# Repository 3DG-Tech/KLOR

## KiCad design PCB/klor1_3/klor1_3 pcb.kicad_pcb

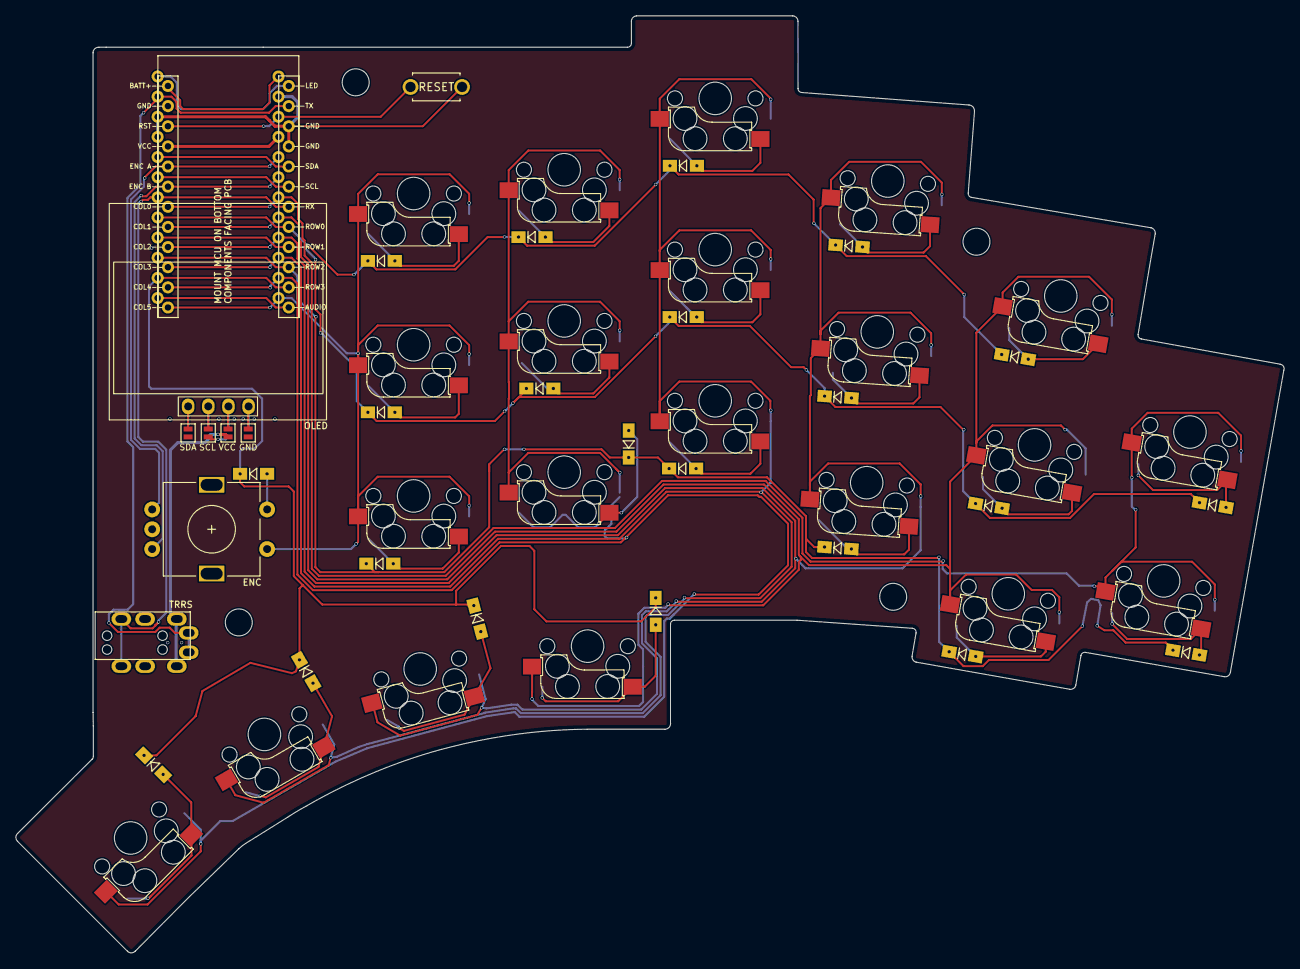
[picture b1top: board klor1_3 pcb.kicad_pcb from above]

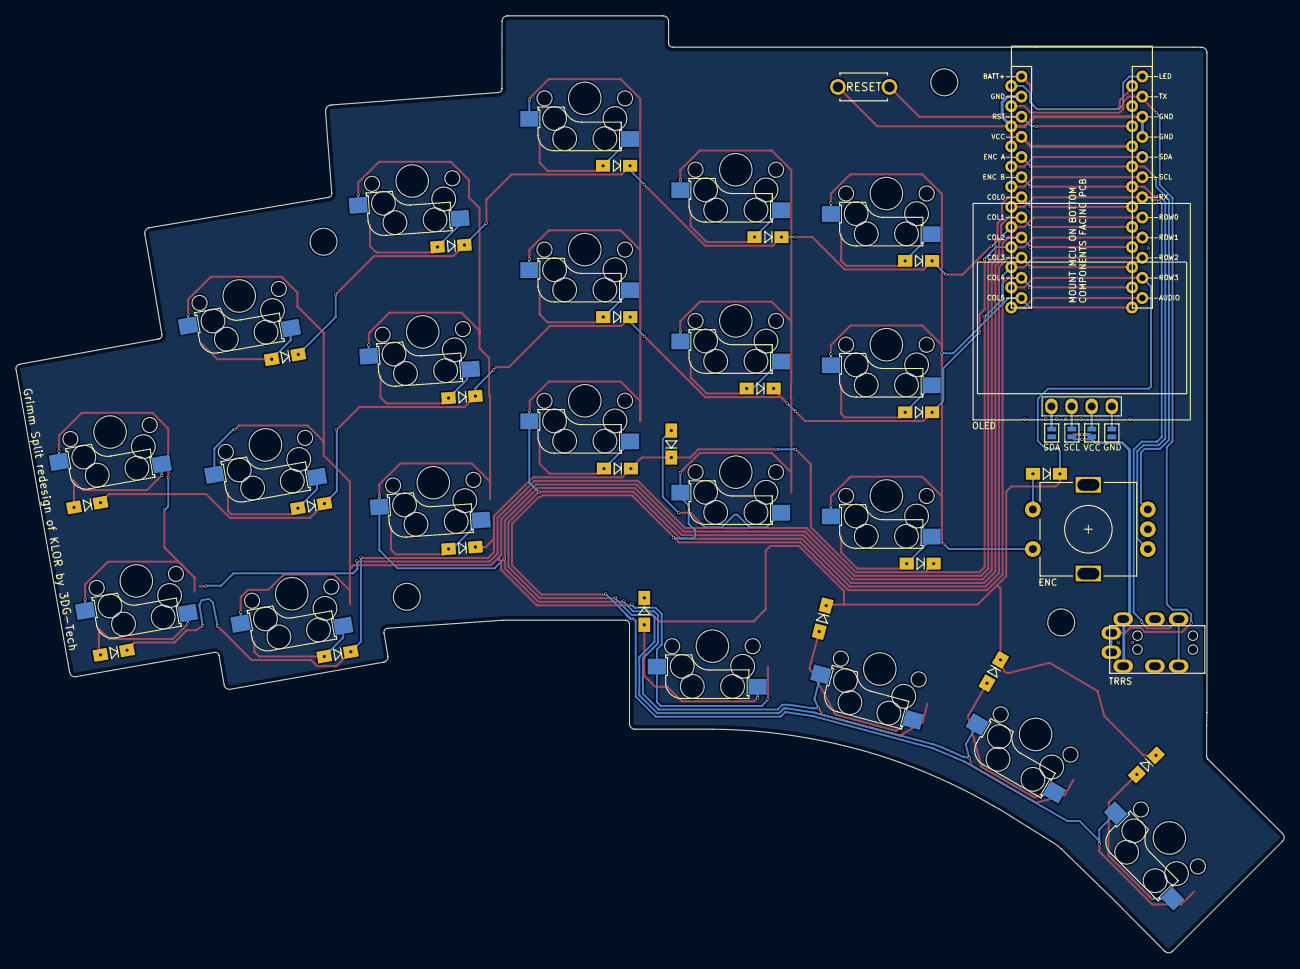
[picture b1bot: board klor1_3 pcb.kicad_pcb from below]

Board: 2 copper layers, 160.0 x 118.2 mm, 60 parts (4 on the bottom side), 45 nets.

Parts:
D1, D2, D3, D4, D5, D6, D7, D8, D9, D10, D11, D12, D13, D14, D15, D16, D17, D18, D19, D20, D21, D22: D_Small; Diode_SOD123
J1: MJ-4PP-9
JP1, JP2, JP3, JP4, JP5, JP6, JP7, JP8: Device_Jumper_NO_Small; Jumper
MH2, MH6, MH8: MountingHole_3.2mm_M3
MH9: MountingHole_2.2mm_M2
OLED1: SSD1306; SSD1306_128x64OLED
RSW1: SW_Push; ResetSW_1side
SW1, SW2, SW3, SW4, SW5, SW6, SW7, SW8, SW9, SW10, SW11, SW12, SW13, SW14, SW15, SW16, SW17, SW19, SW20, SW21, SW22: SW_PUSH-MX_W_LED; SK6812MINI_and_cherry
SW18: RotaryEncoder_Switch; RotaryEncoder_Alps_EC11E-Switch_Vertical_H20mm-keebio_modif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
U1: ProMicro

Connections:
ENCA: SW18.A, U1.20 (F4/A3)
ENCB: SW18.B, U1.19 (F5/A2)
GND: J1.2, JP1.2, JP8.2, RSW1.1, SW18.C, U1.3 (GND), U1.4 (GND), U1.23 (GND)
unnamed: D1.2 (A), SW1.6
unnamed: D2.2 (A), SW2.6
unnamed: D3.2 (A), SW3.6
unnamed: D4.2 (A), SW4.6
unnamed: D5.2 (A), SW5.6
unnamed: D6.2 (A), SW6.6
unnamed: D7.2 (A), SW7.6
unnamed: D8.2 (A), SW8.6
unnamed: D9.2 (A), SW9.6
unnamed: D10.2 (A), SW10.6
unnamed: D11.2 (A), SW11.6
unnamed: D12.2 (A), SW12.6
unnamed: D13.2 (A), SW13.6
unnamed: D14.2 (A), SW14.6
unnamed: D15.2 (A), SW15.6
unnamed: D16.2 (A), SW16.6
unnamed: D17.2 (A), SW17.6
unnamed: D19.2 (A), SW19.6
unnamed: D20.2 (A), SW20.6
unnamed: D21.2 (A), SW21.6
unnamed: D22.2 (A), SW22.6
unnamed: JP1.1, JP5.1, OLED1.1 (GND)
unnamed: JP2.1, JP6.1, OLED1.2 (VCC)
unnamed: JP3.1, JP7.1, OLED1.3 (SCL)
unnamed: JP4.1, JP8.1, OLED1.4 (SDA)
RESET: RSW1.2, U1.22 (RST)
RX: J1.3, U1.7 (4/D4)
SCL: JP3.2, JP6.2, U1.6 (3/D0/SCL)
SDA: JP4.2, JP5.2, U1.5 (2/D1/SDA)
SW18B: D18.2 (A), SW18.S2
TX: J1.4, U1.2 (RX1/D2)
VCC: J1.1, JP2.2, JP7.2, U1.21 (VCC)
col0: SW11.5, SW17.5, U1.18 (F6/A1)
col1: SW5.5, SW10.5, SW16.5, SW22.5, U1.17 (F7/A0)
col2: SW4.5, SW9.5, SW15.5, SW21.5, U1.16 (B1/15)
col3: SW3.5, SW8.5, SW14.5, SW20.5, U1.15 (B3/14)
col4: SW2.5, SW7.5, SW13.5, SW19.5, U1.14 (B2/16)
col5: SW1.5, SW6.5, SW12.5, SW18.S1, U1.13 (B6/10)
row0: D1.1 (K), D2.1 (K), D3.1 (K), D4.1 (K), D5.1 (K), U1.8 (5/C6)
row1: D6.1 (K), D7.1 (K), D8.1 (K), D9.1 (K), D10.1 (K), D11.1 (K), U1.9 (6/D7)
row2: D12.1 (K), D13.1 (K), D14.1 (K), D15.1 (K), D16.1 (K), D17.1 (K), U1.10 (7/E6)
row3: D18.1 (K), D19.1 (K), D20.1 (K), D21.1 (K), D22.1 (K), U1.11 (8/B4)

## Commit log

2024-09-02 more design changes
